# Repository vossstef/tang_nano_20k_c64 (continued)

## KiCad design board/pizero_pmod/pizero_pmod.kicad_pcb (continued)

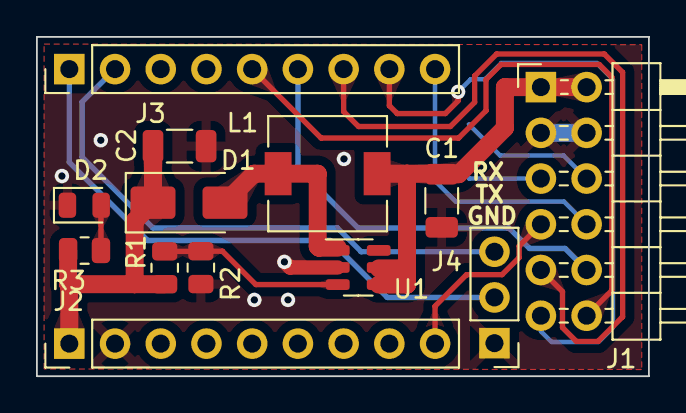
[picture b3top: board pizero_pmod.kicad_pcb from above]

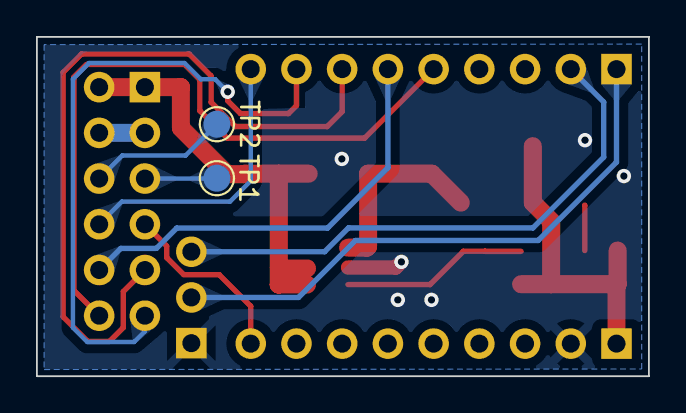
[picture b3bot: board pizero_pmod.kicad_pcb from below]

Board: 2 copper layers, 34.0 x 18.8 mm, 15 parts (2 on the bottom side), 15 nets.

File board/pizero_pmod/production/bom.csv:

"Reference","Value","Comment","LCSC Part #","Qty"
"C1,C2","22uF","1206","C12891","2"
"D1","SS34","SMA","C8678","1"
"D2","green","0805","C2297","1"
"J1","PMOD","2x06, P2.54mm","C60565","1"
"J2,J3","Conn_01x09_Pin","1x09, P2.54mm","C2932701","2"
"J4","Conn_01x03_Pin","1x03, P2.54mm","C2932698","1"
"L1","4.7uH","SMD 6.3x6.3 mm","C142106","1"
"R1","220k","0805","C17556","1"
"R2","30k","0805","C17621","1"
"R3","1k2","0805","C17379","1"
"U1","EA2208","SOT-23-6","C22462489","1"

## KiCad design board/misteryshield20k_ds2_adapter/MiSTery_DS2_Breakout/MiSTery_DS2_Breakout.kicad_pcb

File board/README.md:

# MiSTeryShield20k boards

The MiSTeryNano can be used with off-the-shelf components and
some breadboard setup.

To simplify this this project provides additional
hardware:

Standalone Dock Solution for a BL616 µC M0S DOCK (WIFI):  
[MiSTeryShield20k](https://github.com/harbaum/MiSTeryNano/tree/main/board/misteryshield20k/README.md)

Standalone Dock Solution for a RP2040 µC Raspberry PiPico (WIFI):  
[MiSTeryShield20k RPiPico](/board/misteryshield20k_rpipico/README.md)

Dualshock DS2 Adapter / Cable  
To be to be used with any Dock  
[MiSTeryShield20k DS2 Adapter / Cable](misteryshield20k_ds2_adapter\misteryshield20k_ds2_adapter_cable.md)

[PIZero_PMOD](/board/pizero_pmod/README.md)  
PMOD based on a [RP2040-Zero](https://www.waveshare.com/wiki/RP2040-Zero)  
To be used in conjuction with Primer20k, Primer25k, Mega60k NEO, Mega138k NEO, Mega138kPro

[PIPico_PMOD](/board/pipico_pmod/README.md)  
PMOD based on a [Raspberry Pi Pico W](https://www.raspberrypi.com/documentation/microcontrollers/pico-series.html)  
To be used in conjuction with Primer20k, Primer25k, Mega60k NEO, Mega138k NEO, Mega138kPro

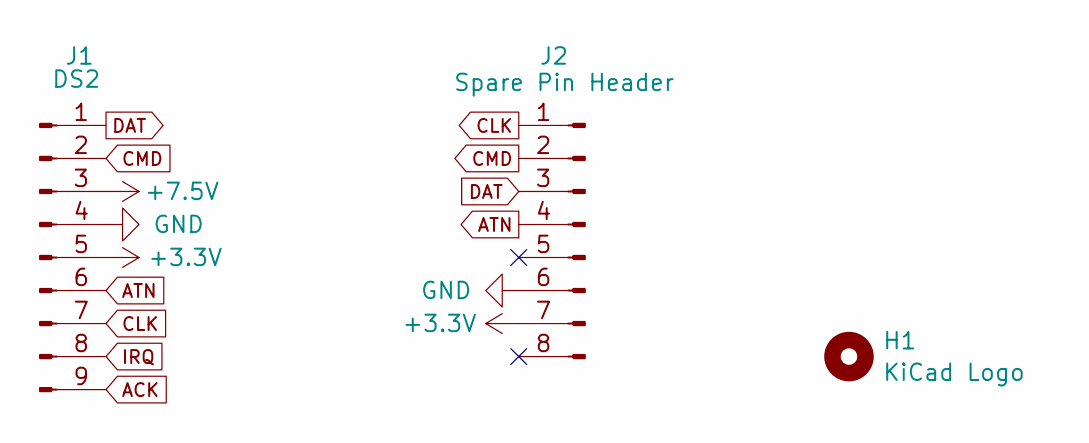
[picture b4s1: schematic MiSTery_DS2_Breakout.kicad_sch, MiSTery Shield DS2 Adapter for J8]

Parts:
H1: KiCad Logo; KiCad-Logo_5mm_SilkScreen
J1: DS2; DS2_Port_Connector
J2: Spare Pin Header; PinHeader_2x04_P2.54mm_Vertical

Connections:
+3.3V: J1.5, J2.7
+7.5V: J1.3
ACK: J1.9
ATN: J1.6, J2.4
CLK: J1.7, J2.1
CMD: J1.2, J2.2
DAT: J1.1, J2.3
GND: J1.4, J2.6
IRQ: J1.8

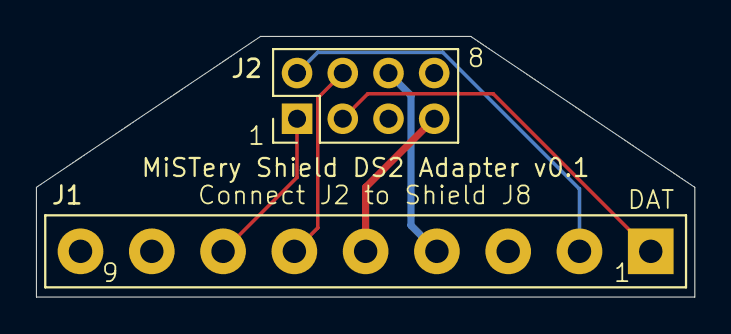
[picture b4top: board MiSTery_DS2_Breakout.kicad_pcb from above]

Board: 2 copper layers, 36.6 x 14.5 mm, 3 parts (1 on the bottom side), 6 nets.

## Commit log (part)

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2024-02-09 good old mist scandoubler included
2024-02-10 osd pause enhancement
2024-02-10 add ds2 as paddle experimental
2024-02-10 video output fixed
2024-02-11 some bugs catched
2024-02-11 inp sel
2024-02-11 further fixes
2024-02-11 readme
2024-02-12 ds2 paddle add
2024-02-12 last fixes
2024-02-12 C1541 dos rom move to spi Flash (#32)
2024-02-15 working
2024-02-15 dram controller adjustment 8 bit width (#38)
2024-02-15 ntsc pll poc
2024-02-18 still a wip
2024-02-18 hdmi catch-up
2024-02-19 wip not working
2024-02-20 single pll demo
2024-02-21 single pll wip
2024-02-21 finally working
2024-02-22 wip nonf
2024-02-22 audio clk adj
2024-02-23 a working wip
2024-02-23 final cleanup
2024-02-23 pal ntsc mode switch (#39)
2024-02-23 bugfix
2024-02-23 bugfix (#42)
2024-02-23 readme updated
2024-02-24 disable incompatible blanking
2024-02-24 wip tp25k
2024-02-25 cleanup
2024-02-25 add 25k readme and photo
2024-02-25 build scripts
2024-02-25 ntsc added
2024-02-25 43 tang primer 25k support (#44)
2024-02-26 documentation update
2024-03-01 add tang mega 138k
2024-03-02 add mega138k
2024-03-05 fixes
2024-03-05 align tm138k
2024-03-06 readme update
2024-03-07 tm138k fix
2024-03-16 installation updated
2024-04-24 loader debugging
2024-04-24 debug only fix tn20 compile script
2024-04-25 tp25k upd
2024-04-25 tm138k upd
2024-04-25 prepare kernal loader
2024-04-27 workaround for debug only
2024-04-28 loader busy added
2024-04-28 adjust
2024-04-29 disable attempt of workaround
2024-04-29 another wip
2024-05-01 loader update
2024-05-01 finalize
2024-05-01 46 cartridge crt file loader support (#49)
2024-05-02 wip working
2024-05-03 fixed
2024-05-03 50 improvements crt prg bin loader (#51)
2024-05-07 drawing and readme update
2024-05-10 wip no sound
2024-05-10 mega
2024-05-11 distorted audio
2024-05-11 tap loader working
2024-05-11 tp25k add
2024-05-11 tm138k
2024-05-12 Sid8580 and tape loader (#54)
2024-05-21 initial
2024-05-24 55 tape sound and userport uart option (#58)
2024-05-25 fixes (#62)
2024-06-11 tn20k dual sid
2024-06-11 2nd sid
2024-06-11 add test bitstream
2024-06-12 dualsid tp25 and tm138k added
2024-06-12 preliminary firmware add
2024-06-13 bugfix_db9_paddle
2024-06-13 Fix D9 joystick and DS Paddle (#67)
2024-06-16 wip2
2024-06-16 wip readm
2024-06-16 Dualsidmister (#68)
2024-06-17 sid filter
2024-06-18 wip disk broken
2024-06-19 fix ntsc
2024-06-20 69 loadable sid filter (#72)
2024-06-22 bugfix 6 drives
2024-06-22 bugfix 6 drives (#73)
2024-06-22 a wip
2024-06-25 store tn20k bitsream
2024-06-25 74 fix buggy release v130 (#75)
2024-06-25 add temporary sid filter curves
2024-07-10 Crt fix (#78)
2024-07-10 fix 25k 138k
2024-07-11 fix_stuck
2024-07-11 fix_stuck (#79)
2024-07-12 catchup release 1.3.2
2024-07-22 add raw uart
2024-08-29 usb paddle
2024-08-31 paddle
2024-09-04 USB Gamepad as paddle (#85)
2024-09-08 documentation update (#86)
2024-09-10 uart hw pin interface
2024-09-11 ext uart pin
2024-09-11 UART HW pin Interface (#87)
2024-10-04 enhanement
2024-10-04 enhanement (#92)
2024-10-04 extra button fix
2024-10-18 multicard fix
2024-10-18 multicard fix (#94)
2024-10-19 freezer fix
2024-10-19 freezer fix for action CRT cards (#95)
2024-10-19 json
2024-10-20 crt_unload companion fix
2024-10-20 crt_unload companion fix (#96)
2024-10-20 crt_unload companion-fix
2024-10-22 ntsc switch
2024-10-22 wip sw
2024-10-22 wip update misc
2024-10-22 3c led fix
2024-10-22 debug led
2024-10-24 tp25k
2024-10-24 Ntsc fix (#98)
2024-10-25 fix design db
2024-10-25 fix design db (#99)
2024-10-25 tn25k tfcard v2
2024-10-25 tn25k tfcard v2 (#100)
2024-10-28 fix lag
2024-10-28 fix lag issue (#103)
2024-11-01 wip1
2024-11-01 Bugfix (#105)
2024-11-02 fix_ntec_noise
2024-11-02 fix_ntsc_noise2
2024-11-02 fix_ntsc_noise (#108)
2024-11-02 furter fix
2024-11-02 furter fix (#109)
2024-11-05 tm60k
2024-11-05 tm60k (#110)
2024-11-06 cleanup (#111)
2024-11-07 tm60k fix c1541 and led
2024-11-07 tm60k fix c1541 and led (#112)
2024-11-08 dual ds2 interface
2024-11-10 tm60k neo tm138k pro
2024-11-11 m138kpro
2024-11-12 dual ds2 interface (#113)
2024-11-14 tm60k tm138k dual ds2
2024-11-14 tm60k tm138k dual ds2 (#114)
2024-11-19 build update
2024-12-01 tm60 fix
2024-12-01 tm60 fix (#115)
2024-12-21 tn20k lcd
2024-12-28 qsim
2024-12-28 qsim (#117)
2025-01-01 lcd ds2
2025-01-15 LCD (#118)
2025-02-01 tm138kpro lcd
2025-02-05 MisteryShield20k_RPiPico
2025-02-05 MisteryShield20k_RPiPico (#120)
2025-02-06 flash gw5a fix
2025-02-06 flash fix
2025-02-07 flash_fix
2025-02-07 Flash fix (#122)
2025-02-09 README lint
2025-02-24 readme board
2025-02-25 board readme and picture
2025-02-26 MiSTeryShield20kRPiPico_V2
2025-02-27 usb paddle mode fix
2025-02-28 usb paddle mode fix (#126)
2025-03-15 3D Model
2025-03-17 serialif
2025-03-19 pizero pcba design
2025-03-19 pizero
2025-03-19 pizero pcba design (#130)
2025-03-21 pizero documentation
2025-03-22 add 6551
2025-03-25 uart6551
2025-03-25 wip io
2025-03-25 wip io ctrl
2025-03-26 6551 adjust
2025-03-27 wip nonw
2025-03-28 add xml
2025-03-28 first working
2025-03-28 midi disable
2025-03-28 misteryshield20k_rpipicousb
2025-03-28 u6551
2025-03-28 SwiftLink 6551 with SPI_SYS_PORT Access (#131)
2025-03-29 fix6551
2025-03-29 fix6551 (#132)
2025-03-29 add updated shield (DS2 removed)
2025-03-29 Shieldnods2 (#133)
2025-03-30 documentation
2025-04-05 pmod_zero
2025-04-07 g6551 slowdown
2025-04-08 g6551 adj baud
2025-04-08 u6551 prog baudrate
2025-04-10 u6551 cleanup
2025-04-10 readme feature list
2025-04-17 u6551 speedup
2025-04-26 console60k
2025-04-27 Console60k (#139)
2025-04-28 Console60k fd (#140)
2025-04-29 keyboard improvement
2025-04-30 shiftkeys
2025-05-03 keyshift
2025-05-03 shifkeys
2025-05-03 keyboard improvement (#141)
    Auto shift press for Function Key F2, F4, F6, F8, Cursor UP / LEFT and INSERT
    Keyboard Key corrections HOME, INSERT, DELETE
    Cartridge support for Waterloo Structured BASIC and BMP-Data Turbo 2000
    Numpad Joystick moved to Core
2025-05-07 keyboard_bw_reading
2025-05-08 kbd_bw_reading
2025-05-08 keyboard matrix removal
2025-05-08 kbd matrix
2025-05-09 xml upd
2025-05-09 kbd bw reading
2025-05-10 kbd bw
2025-05-10 Kbd bw reading (#143)
2025-05-10 detach reset fix
2025-06-12 link added
2025-06-15 kbd trigger
2025-06-15 kbd trigger (#147)
2025-07-17 tc60k and tn20k internal bl616
2025-07-17 tc60k and tn20k internal bl616 (#149)
2025-08-01 tc60k pinmap
2025-08-01 tc60k pinmap (#153)
2025-08-09 board update
2025-08-09 board update (#156)
